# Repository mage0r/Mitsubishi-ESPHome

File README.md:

# Mitsubishi ESPHome
 Controller board for Mitsubishi ESPHome 

Having 5 of these units and recently going way to deep on the whole Solar + Home Assistant I looked for a simple circuit I could just plug in and move on with my life.

I couldn't find one.  Everything was jamming some pins on a D1 mini or overkilling it with a Raspberry Pi.

So I looked really, really closely at:
https://chrdavis.github.io/hacking-a-mitsubishi-heat-pump-Part-1/
https://nicegear.nz/blog/hacking-a-mitsubishi-heat-pump-air-conditioner/

And used them to design my own.

To do the inital program for this you will need a Superhouse.tv ESPFlasher (https://www.superhouse.tv/product/espflasher-esp8266-esp32-usb-serial-flasher/)

I've included a config example for ESPHome.

To integrate this with Home Assistant.
https://github.com/echavet/MitsubishiCN105ESPHome

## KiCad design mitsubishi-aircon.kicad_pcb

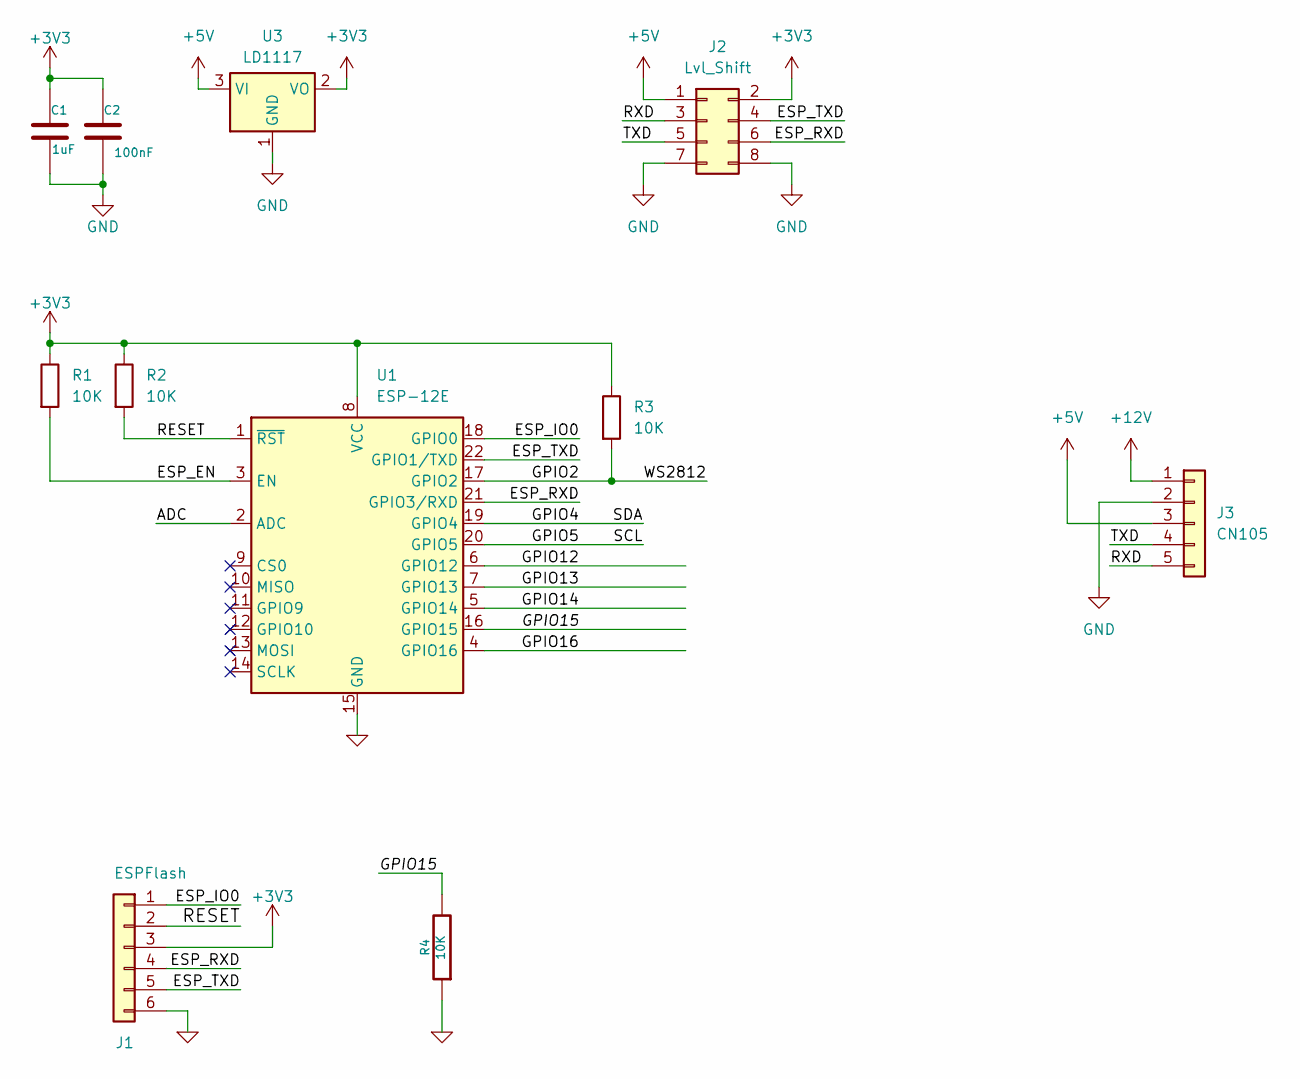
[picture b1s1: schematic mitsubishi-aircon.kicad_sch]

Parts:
C1: 1uF; C_0603_1608Metric_Pad1.08x0.95mm_HandSolder
C2: 100nF; C_0603_1608Metric_Pad1.08x0.95mm_HandSolder
J1: ESPFlash
J2: Lvl_Shift; lvl_shift
J3: CN105; PinHeader_1x05_P2.54mm_Vertical
R1, R2, R3, R4: 10K; R_0603_1608Metric_Pad0.98x0.95mm_HandSolder
U1: ESP-12E
U3: LD1117; SOT-223-3_TabPin2

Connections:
+3V3: C1.1, C2.1, J1.3, J2.2, R1.1, R2.1, R3.1, U1.8 (VCC), U3.2 (VO)
+5V: J2.1, J3.3, U3.3 (VI)
+12V: J3.1
/ADC: U1.2 (ADC)
/ESP_EN: R1.2, U1.3 (EN)
/ESP_IO0: J1.1, U1.18 (GPIO0)
/ESP_RXD: J1.4, J2.6, U1.21 (GPIO3/RXD)
/ESP_TXD: J1.5, J2.4, U1.22 (GPIO1/TXD)
/GPIO2: R3.2, U1.17 (GPIO2)
/GPIO4: U1.19 (GPIO4)
/GPIO5: U1.20 (GPIO5)
/GPIO12: U1.6 (GPIO12)
/GPIO13: U1.7 (GPIO13)
/GPIO14: U1.5 (GPIO14)
/GPIO15: R4.2, U1.16 (GPIO15)
/GPIO16: U1.4 (GPIO16)
/RESET: J1.2, R2.2, U1.1 (~RST)
/RXD: J2.3, J3.5
/TXD: J2.5, J3.4
GND: C1.2, C2.2, J1.6, J2.7, J2.8, J3.2, R4.1, U1.15 (GND), U3.1 (GND)

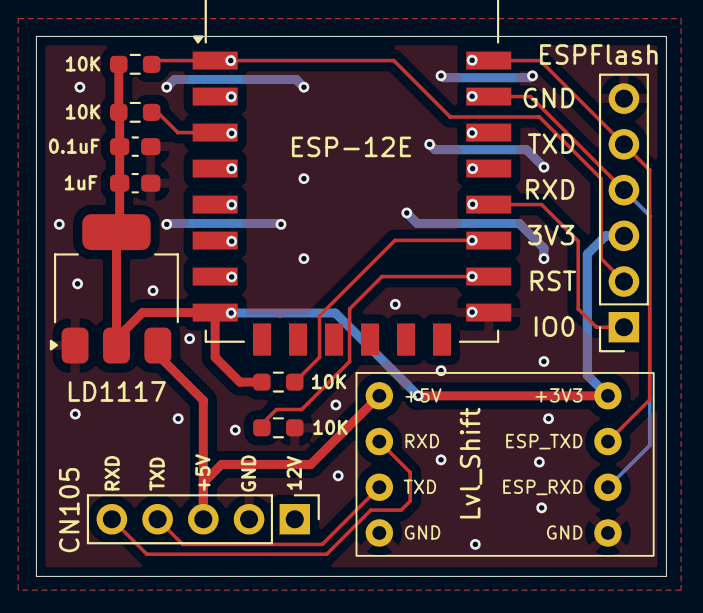
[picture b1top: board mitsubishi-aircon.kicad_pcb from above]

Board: 2 copper layers, 35.0 x 30.0 mm, 11 parts (0 on the bottom side), 12 nets.

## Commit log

2024-11-04 Circuit board to connect Mitsubish Aircon to ESPHome
2024-11-14 Adding some photos
